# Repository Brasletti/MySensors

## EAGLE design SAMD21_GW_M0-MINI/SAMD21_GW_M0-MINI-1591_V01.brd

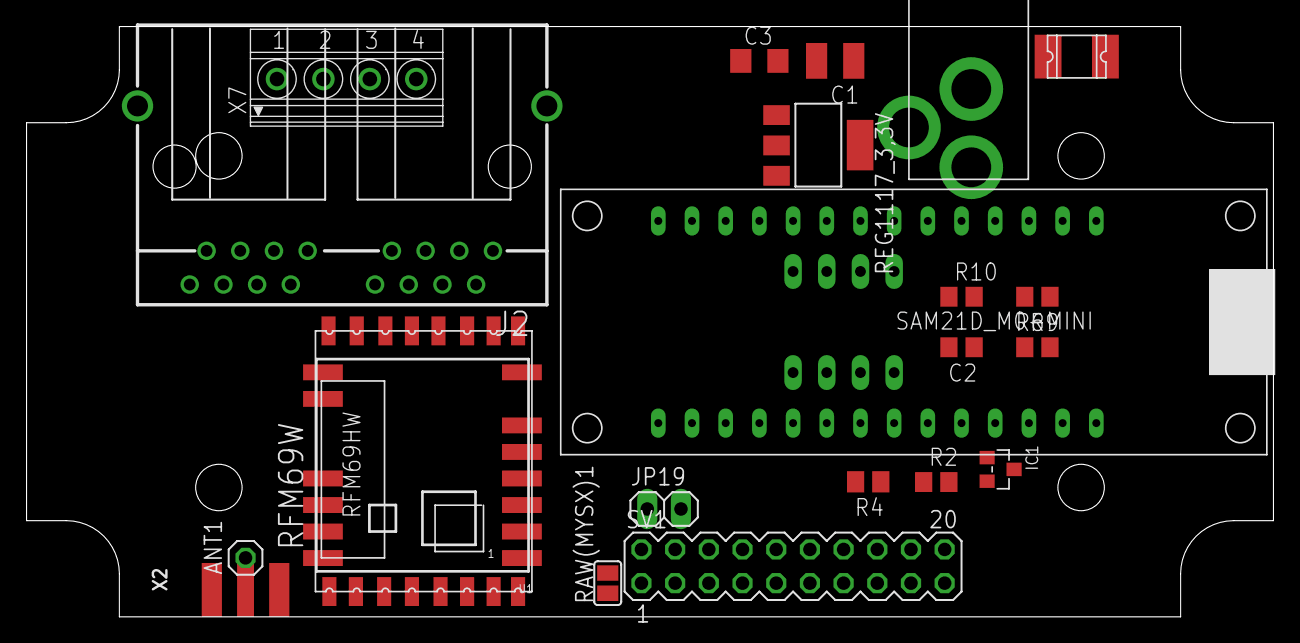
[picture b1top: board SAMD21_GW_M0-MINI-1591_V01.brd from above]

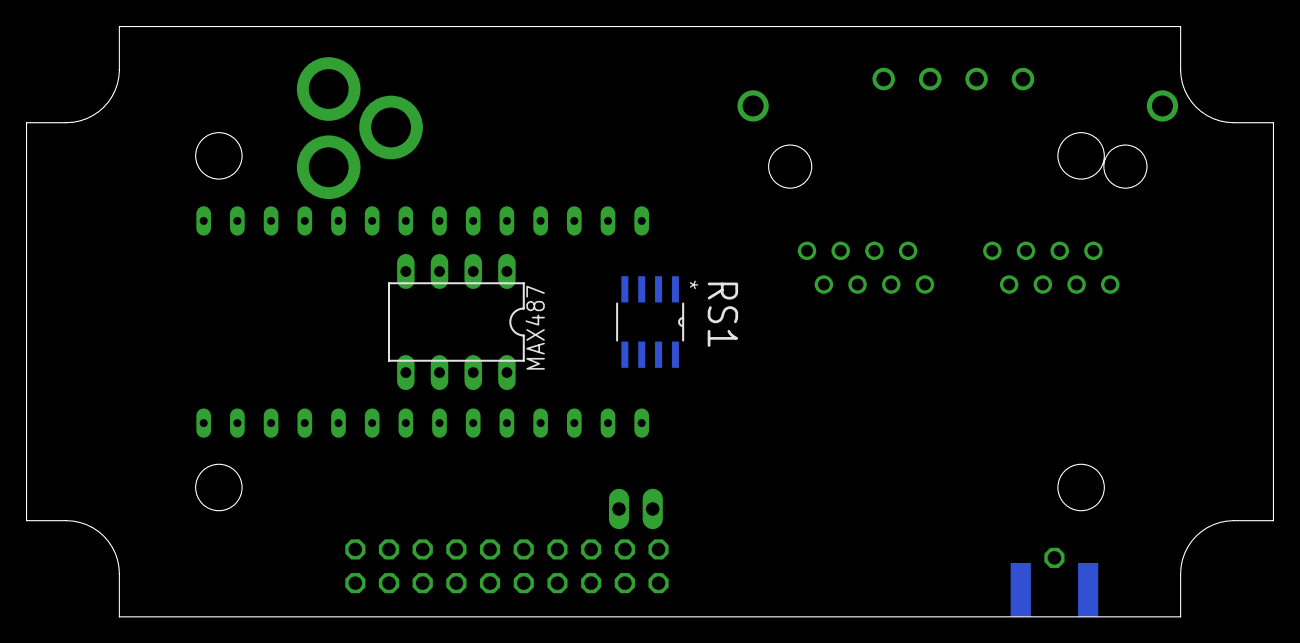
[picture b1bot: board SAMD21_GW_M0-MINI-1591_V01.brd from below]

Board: 2 copper layers, 94.0 x 44.5 mm, 25 parts (2 on the bottom side), 25 nets, no tracks yet.

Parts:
ANT1: 1X01
C1: 10uF; C1210
C2: 22p; C0805
C3: 0.1uF; C1206
F1: 1812L
IC1: ATSHA204A; SOT23
J2: 557570-1
JP19: 1X02
M0-MINI1: SAM21D_M0-MINI; SAMD21_M0-MINI
MAX487: MAX481CPA; DIL08
R2: R0805
R4: 10k; M0805
R6: 150R; R0805
R9, R10: 330R; R0805
RAW(MYSX)1: open; SJ
REG1117_3,3V: REG1117; SOT223
RFM69W: RFM69HW; RFM
RS1: MAX487ECSA+; SOIC127P600X175-8N
SV1: MA10-2
U1: RFM69HCW; RFM69HCW-XXXS2
U$2: 1591XXA
U$3: 2.1MMJACKTHM; PJ-102A
X2: SMA_EDGELAUNCH
X7: 1751264

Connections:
5V: C2.2, M0-MINI1.VIN, R9.1, RS1.8
A: J2.1-1, J2.2-1, MAX487.6, R6.1, R9.2, RS1.6, X7.2
A0: M0-MINI1.A0, SV1.8
A3: M0-MINI1.A3, SV1.15
A4: M0-MINI1.A4, SV1.16
ANT: ANT1.1, RFM69W.ANT, U1.ANT, X2.P
B: J2.1-2, J2.2-2, MAX487.7, R6.2, R10.1, RS1.7, X7.3
D3: M0-MINI1.D3, R2.1, SV1.9
D4/IRQ: M0-MINI1.IRQ, RFM69W.DIO0, RS1.2, RS1.3, SV1.10, U1.DIO0
D5: M0-MINI1.D5, SV1.11
D6: M0-MINI1.D6, SV1.12
D7/ATSHA: IC1.1, M0-MINI1.D7, SV1.13
D8: M0-MINI1.D8, SV1.14
D10/SS: M0-MINI1.D10/SS, R4.1, RFM69W.NSS, SV1.20, U1.NSS
D11/MOSI: M0-MINI1.D11/MOSI, RFM69W.MOSI, SV1.17, U1.MOSI
D12/MISO: M0-MINI1.D12/MISO, RFM69W.MISO, SV1.18, U1.MISO
D13/SCK: M0-MINI1.D13/SCK, RFM69W.SCK, SV1.19, U1.SCK
GND: C1.2, C2.1, C3.2, IC1.3, J2.1-6, J2.1-8, J2.2-6, J2.2-8, JP19.1, M0-MINI1.GND1, M0-MINI1.GND2, MAX487.5, R10.2, REG1117_3,3V.1, RFM69W.GNDA, RFM69W.GNDB, RS1.5, SV1.4, U1.GND_1, U1.GND_2, U1.GND_3, U$3.RING, X2.GND@1, X2.GND@2, X2.GND@3, X2.GND@4, X7.4
IN: C3.1, F1.P$1, J2.1-3, J2.1-7, J2.2-3, J2.2-7, RAW(MYSX)1.1, REG1117_3,3V.3, X7.1
RAW: RAW(MYSX)1.2, SV1.1
RESET: M0-MINI1.RST, SV1.7
RX: M0-MINI1.D0/RX, RS1.1, SV1.6
TX: M0-MINI1.D1/TX, RS1.4, SV1.5
VCC: C1.1, IC1.2, JP19.2, M0-MINI1.VCC, MAX487.8, R2.2, R4.2, REG1117_3,3V.2, RFM69W.VCC, SV1.3, U1.3.3V
VIN: F1.P$2, U$3.TIP

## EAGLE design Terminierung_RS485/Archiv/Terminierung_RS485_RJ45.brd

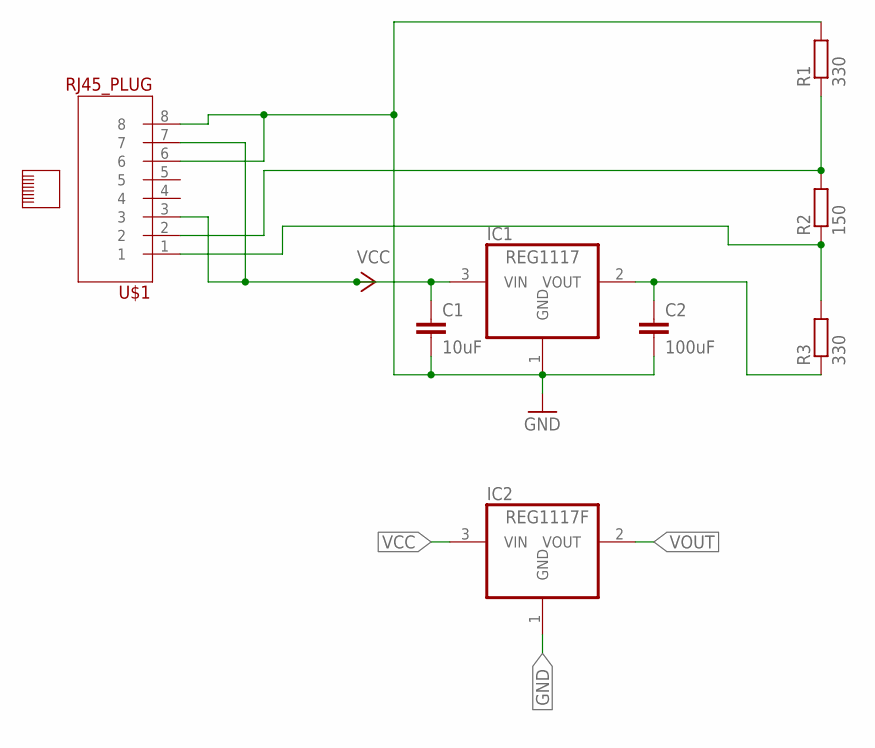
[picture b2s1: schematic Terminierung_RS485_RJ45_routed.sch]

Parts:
C1: 10uF; C0805K
C2: 100uF; C0805K
IC1: REG1117; SOT223
IC2: REG1117F; DD-3
R1, R3: 330; R0805
R2: 150; R0805
U$1: RJ45_PLUG

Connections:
GND: C1.2, C2.2, IC1.1 (GND), IC2.1 (GND), R1.2, U$1.6, U$1.8
unnamed: R1.1, R2.2, U$1.2
unnamed: R2.1, R3.2, U$1.1
VCC: C1.1, IC1.3 (VIN), IC2.3 (VIN), U$1.3, U$1.7
VOUT: C2.1, IC1.2 (VOUT), IC2.2 (VOUT), R3.1

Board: 2 copper layers, 8 parts (4 on the bottom side), 5 nets, no tracks yet.
